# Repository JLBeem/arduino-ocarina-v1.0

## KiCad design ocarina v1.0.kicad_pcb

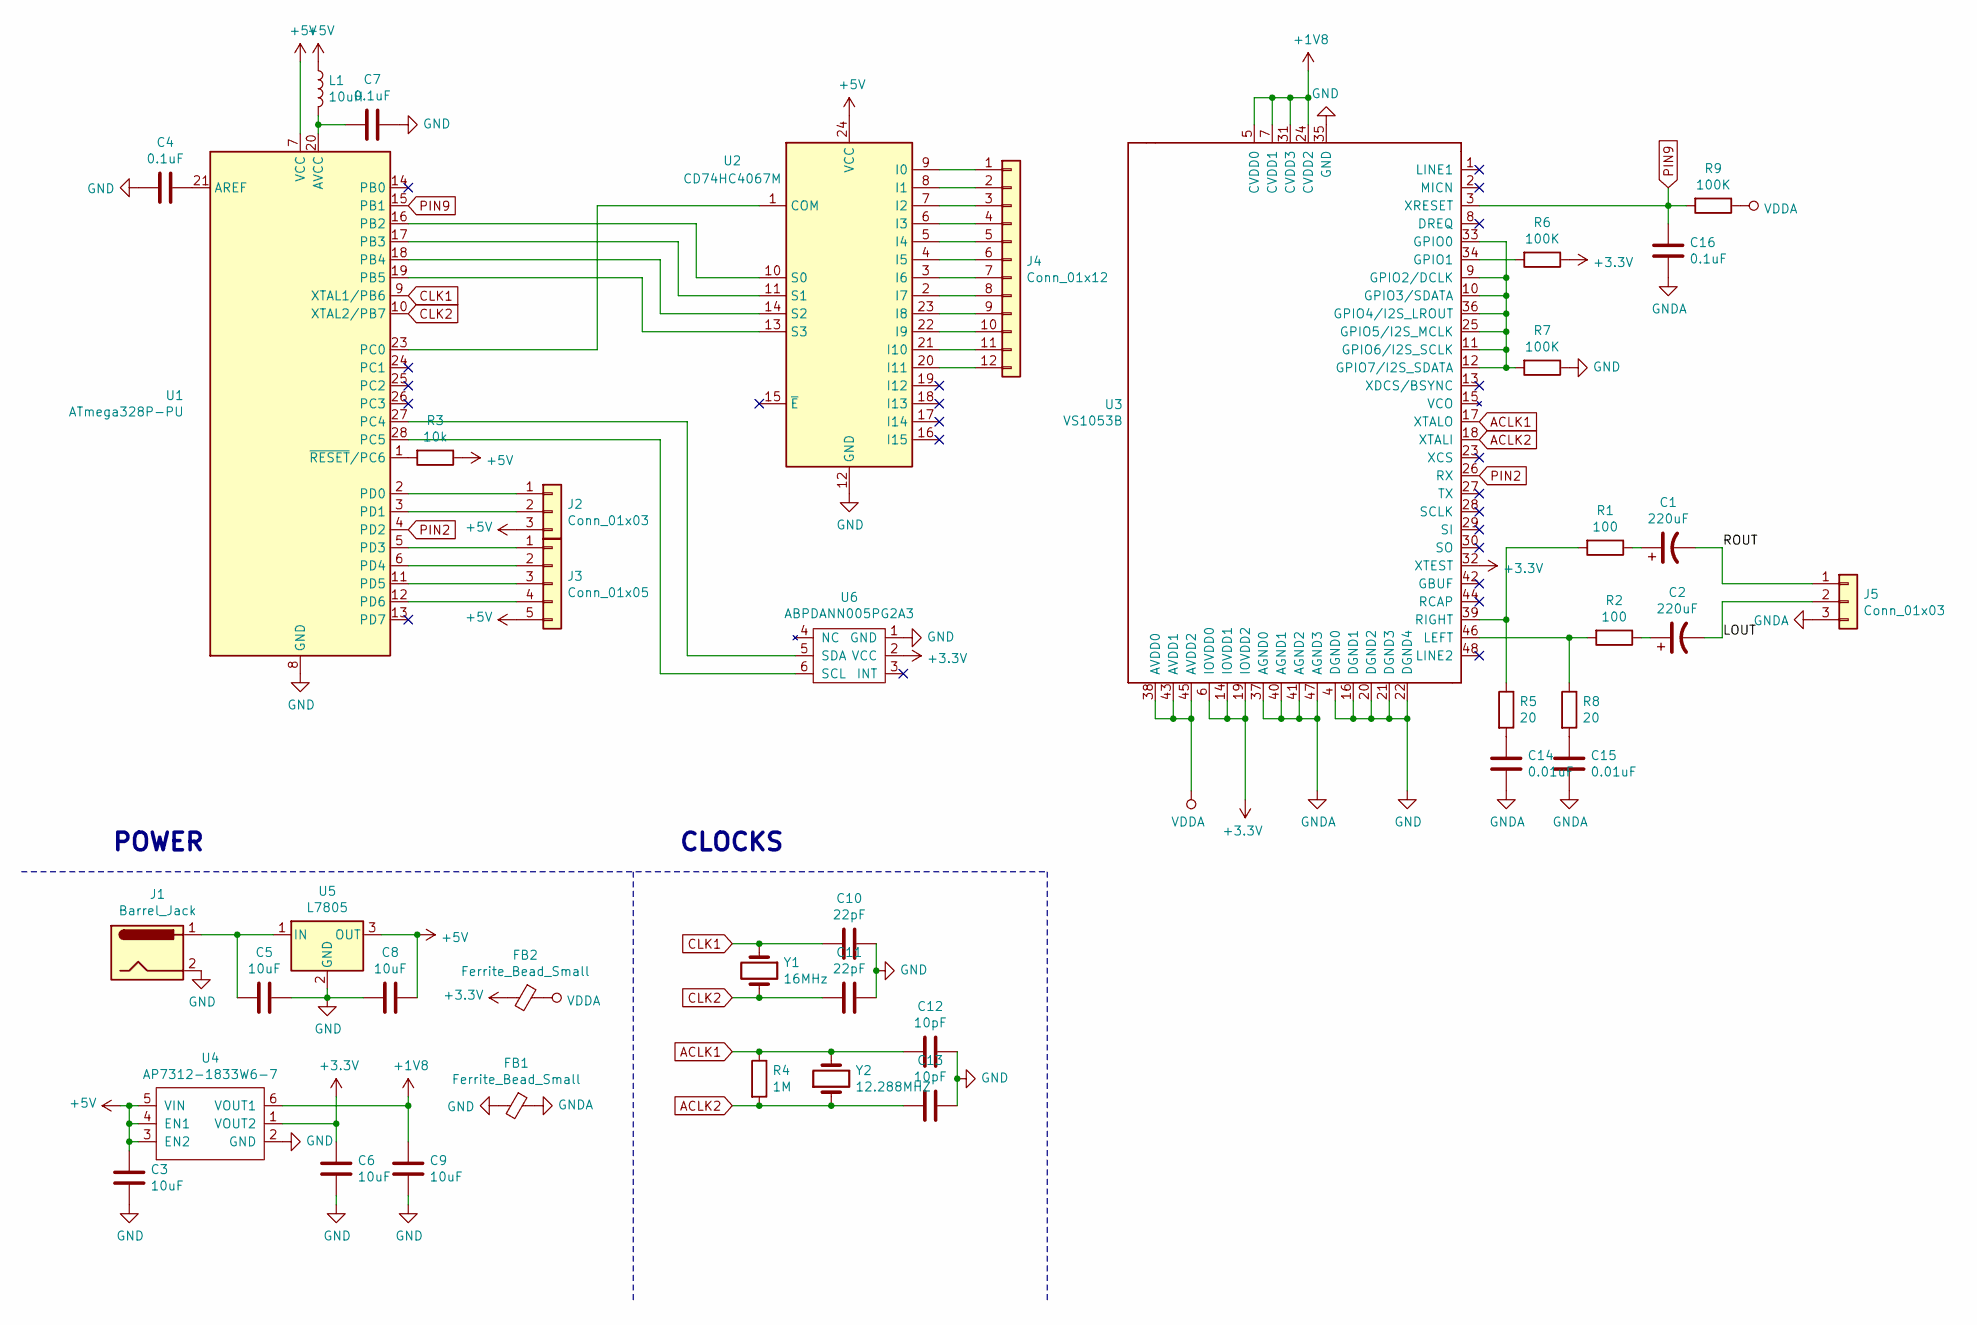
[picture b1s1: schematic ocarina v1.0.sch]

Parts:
C1, C2: 220uF; CP_Radial_D16.0mm_P7.50mm
C3, C5, C6, C8, C9: 10uF; C_0805_2012Metric_Pad1.15x1.40mm_HandSolder
C4, C7, C16: 0.1uF; C_0603_1608Metric_Pad1.05x0.95mm_HandSolder
C10, C11: 22pF; C_0603_1608Metric_Pad1.05x0.95mm_HandSolder
C12, C13: 10pF; C_0603_1608Metric_Pad1.05x0.95mm_HandSolder
C14, C15: 0.01uF; C_0603_1608Metric_Pad1.05x0.95mm_HandSolder
FB1, FB2: Ferrite_Bead_Small; L_0805_2012Metric_Pad1.15x1.40mm_HandSolder
J1: Barrel_Jack; BarrelJack_CUI_PJ-036AH-SMT_Horizontal
J2: Conn_01x03; PinHeader_1x03_P2.00mm_Vertical
J3: Conn_01x05; PinSocket_1x05_P2.00mm_Vertical
J4: Conn_01x12; PinSocket_1x12_P2.00mm_Vertical
J5: Conn_01x03; PinSocket_1x03_P2.00mm_Vertical
L1: 10uH; L_Radial_D8.7mm_P5.00mm_Fastron_07HCP
R1, R2: 100; R_0603_1608Metric_Pad1.05x0.95mm_HandSolder
R3: 10k; R_0603_1608Metric_Pad1.05x0.95mm_HandSolder
R4: 1M; R_0603_1608Metric_Pad1.05x0.95mm_HandSolder
R5, R8: 20; R_0603_1608Metric_Pad1.05x0.95mm_HandSolder
R6, R7, R9: 100K; R_0805_2012Metric_Pad1.15x1.40mm_HandSolder
U1: ATmega328P-PU; DIP-28_W7.62mm
U2: CD74HC4067M; SOIC-24W_7.5x15.4mm_P1.27mm
U3: VS1053B
U4: AP7312-1833W6-7; SOT-23-6_Handsoldering
U5: L7805; SOT-223
U6: ABPDANN005PG2A3; pressure_sensor
Y1: 16MHz; Crystal_HC49-U_Vertical
Y2: 12.288MHZ; Crystal_HC49-U_Vertical

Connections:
+1V8: C9.1, U3.5 (CVDD0), U3.7 (CVDD1), U3.24 (CVDD2), U3.31 (CVDD3), U4.6 (VOUT1)
+3V3: C6.1, FB2.2, R6.1, U3.6 (IOVDD0), U3.14 (IOVDD1), U3.19 (IOVDD2), U3.32 (XTEST), U4.1 (VOUT2), U6.2 (VCC)
+5V: C3.1, C8.1, J2.3, J3.5, L1.1, R3.1, U1.7 (VCC), U2.24 (VCC), U4.3 (EN2), U4.4 (EN1), U4.5 (VIN), U5.3 (OUT)
/LOUT: C2.2, J5.2
/ROUT: C1.2, J5.1
ACLK1: C12.1, R4.1, U3.17 (XTALO), Y2.2
ACLK2: C13.1, R4.2, U3.18 (XTALI), Y2.1
CLK1: C10.2, U1.9 (XTAL1/PB6), Y1.1
CLK2: C11.2, U1.10 (XTAL2/PB7), Y1.2
GND: C3.2, C4.2, C5.1, C6.2, C7.1, C8.2, C9.2, C10.1, C11.1, C12.2, C13.2, FB1.2, J1.2, R7.1, U1.8 (GND), U1.22 (GND), U2.12 (GND), U3.4 (DGND0), U3.16 (DGND1), U3.20 (DGND2), U3.21 (DGND3), U3.22 (DGND4), U3.35 (GND), U4.2 (GND), U5.2 (GND), U6.1 (GND)
GNDA: C14.2, C15.2, C16.2, FB1.1, J5.3, U3.37 (AGND0), U3.40 (AGND1), U3.41 (AGND2), U3.47 (AGND3)
unnamed: C1.1, R1.1
unnamed: C2.1, R2.1
unnamed: C4.1, U1.21 (AREF)
unnamed: C5.2, J1.1, U5.1 (IN)
unnamed: C7.2, L1.2, U1.20 (AVCC)
unnamed: C14.1, R5.2
unnamed: C15.1, R8.2
unnamed: J2.1, U1.2 (PD0)
unnamed: J2.2, U1.3 (PD1)
unnamed: J3.1, U1.5 (PD3)
unnamed: J3.2, U1.6 (PD4)
unnamed: J3.3, U1.11 (PD5)
unnamed: J3.4, U1.12 (PD6)
unnamed: J4.1, U2.9 (I0)
unnamed: J4.2, U2.8 (I1)
unnamed: J4.3, U2.7 (I2)
unnamed: J4.4, U2.6 (I3)
unnamed: J4.5, U2.5 (I4)
unnamed: J4.6, U2.4 (I5)
unnamed: J4.7, U2.3 (I6)
unnamed: J4.8, U2.2 (I7)
unnamed: J4.9, U2.23 (I8)
unnamed: J4.10, U2.22 (I9)
unnamed: J4.11, U2.21 (I10)
unnamed: J4.12, U2.20 (I11)
unnamed: R1.2, R5.1, U3.39 (RIGHT)
unnamed: R2.2, R8.1, U3.46 (LEFT)
unnamed: R3.2, U1.1 (~RESET~/PC6)
unnamed: R6.2, U3.34 (GPIO1)
unnamed: R7.2, U3.9 (GPIO2/DCLK), U3.10 (GPIO3/SDATA), U3.11 (GPIO6/I2S_SCLK), U3.12 (GPIO7/I2S_SDATA), U3.25 (GPIO5/I2S_MCLK), U3.33 (GPIO0), U3.36 (GPIO4/I2S_LROUT)
unnamed: U1.16 (PB2), U2.10 (S0)
unnamed: U1.17 (PB3), U2.11 (S1)
unnamed: U1.18 (PB4), U2.14 (S2)
unnamed: U1.19 (PB5), U2.13 (S3)
unnamed: U1.23 (PC0), U2.1 (COM)
unnamed: U1.27 (PC4), U6.5 (SDA)
unnamed: U1.28 (PC5), U6.6 (SCL)
PIN2: U1.4 (PD2), U3.26 (RX)
PIN9: C16.1, R9.2, U1.15 (PB1), U3.3 (XRESET)
VDDA: FB2.1, R9.1, U3.38 (AVDD0), U3.43 (AVDD1), U3.45 (AVDD2)

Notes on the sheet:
POWER
CLOCKS

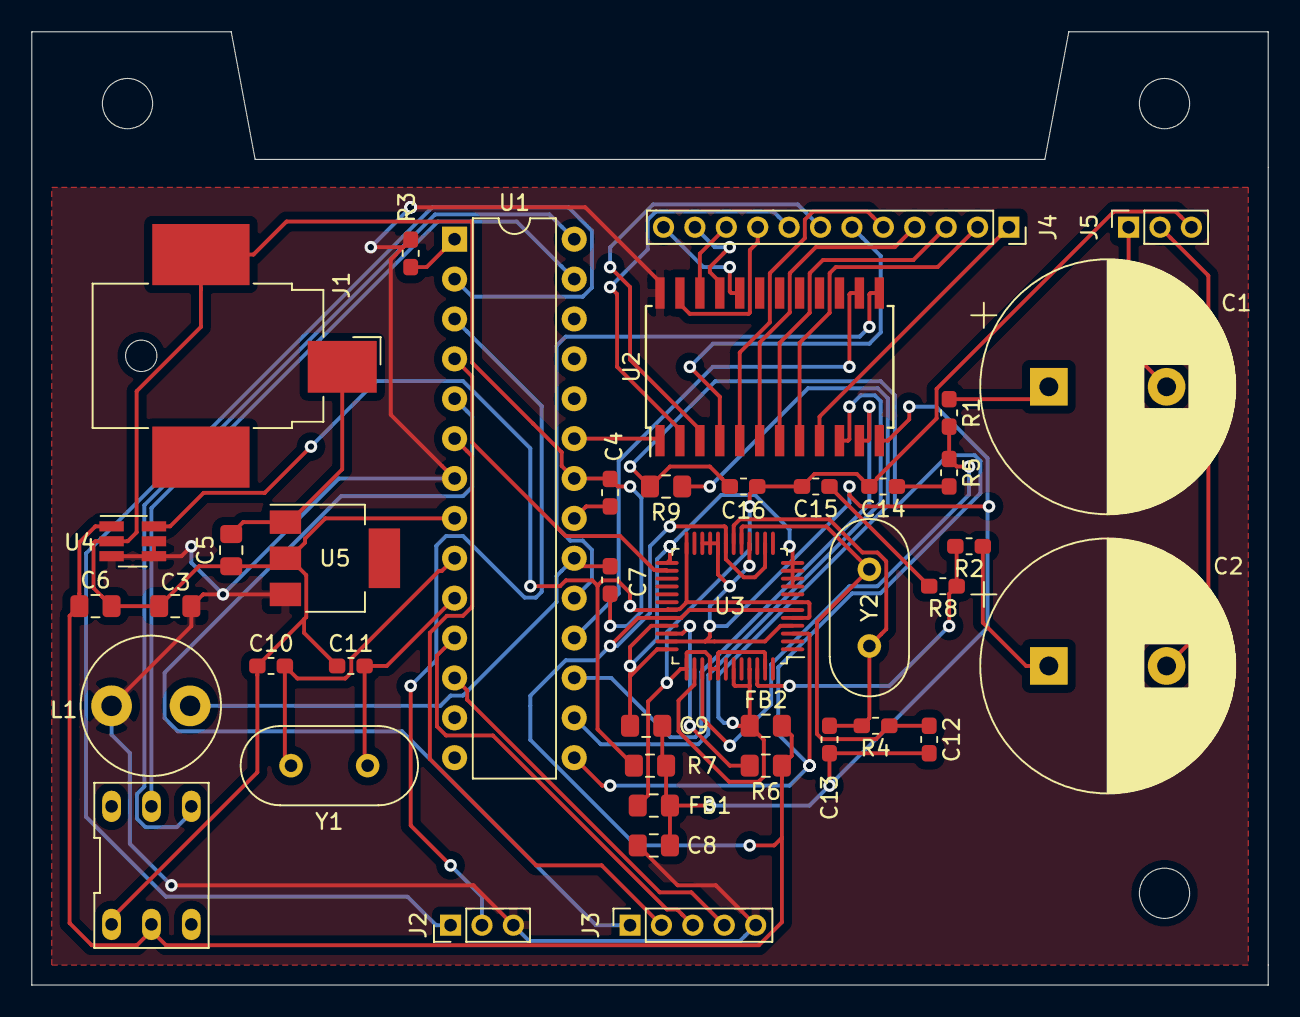
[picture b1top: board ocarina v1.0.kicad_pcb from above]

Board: 2 copper layers, 78.7 x 60.7 mm, 41 parts (0 on the bottom side), 51 nets.

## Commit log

2022-01-25 Full file upload
